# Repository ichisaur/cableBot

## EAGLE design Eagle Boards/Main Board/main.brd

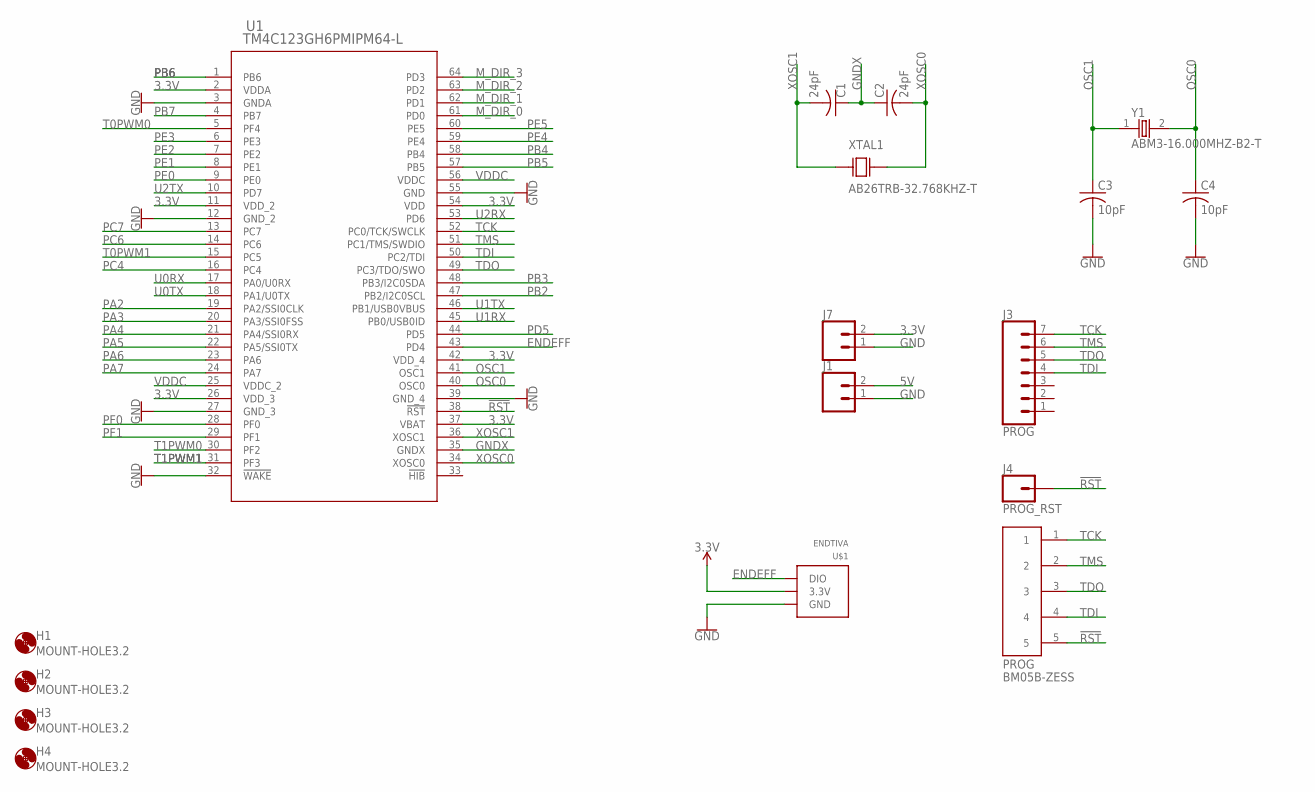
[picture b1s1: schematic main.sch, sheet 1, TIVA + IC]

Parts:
C1, C2: 24pF; C0805
C3, C4: 10pF; C0805
H1, H2, H3, H4: MOUNT-HOLE3.2; 3,2
J1, J7: CONN_02; 1X02
J3: PROG; 1X07
J4: PROG_RST; 1X01
PROG: BM05B-ZESS
U1: TM4C123GH6PMIPM64-L; PM64-L
U$1: ENDTIVA
XTAL1: AB26TRB-32.768KHZ-T; XTAL_AB26TRB-32.768KHZ-T
Y1: ABM3-16.000MHZ-B2-T; XTAL500X320X130N

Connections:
3.3V: J7.2, U1.2 (VDDA), U1.11 (VDD_2), U1.26 (VDD_3), U1.37 (VBAT), U1.42 (VDD_4), U1.54 (VDD), U$1.3.3V; also elsewhere on the board
5V: J1.2; also elsewhere on the board
!RST: J4.1, PROG.5, U1.38 (!RST); also elsewhere on the board
ENDEFF: U1.43 (PD4), U$1.DIO
GND: C3.2, C4.2, J1.1, J7.1, U1.3 (GNDA), U1.12 (GND_2), U1.27 (GND_3), U1.32 (!WAKE), U1.39 (GND_4), U1.55 (GND), U$1.GND; also elsewhere on the board
GNDX: C1.1, C2.1, U1.35 (GNDX)
M_DIR_0: U1.61 (PD0); also elsewhere on the board
M_DIR_1: U1.62 (PD1); also elsewhere on the board
M_DIR_2: U1.63 (PD2); also elsewhere on the board
M_DIR_3: U1.64 (PD3); also elsewhere on the board
OSC0: C4.1, U1.40 (OSC0), Y1.2
OSC1: C3.1, U1.41 (OSC1), Y1.1
PA2: U1.19 (PA2/SSI0CLK)
PA3: U1.20 (PA3/SSI0FSS)
PA4: U1.21 (PA4/SSI0RX)
PA5: U1.22 (PA5/SSI0TX)
PA6: U1.23 (PA6)
PA7: U1.24 (PA7)
PB2: U1.47 (PB2/I2C0SCL)
PB3: U1.48 (PB3/I2C0SDA)
PB4: U1.58 (PB4)
PB5: U1.57 (PB5)
PB6: U1.1 (PB6)
PB7: U1.4 (PB7)
PC4: U1.16 (PC4)
PC6: U1.14 (PC6)
PC7: U1.13 (PC7)
PD5: U1.44 (PD5)
PE0: U1.9 (PE0)
PE1: U1.8 (PE1)
PE2: U1.7 (PE2)
PE3: U1.6 (PE3)
PE4: U1.59 (PE4)
PE5: U1.60 (PE5)
PF0: U1.28 (PF0)
PF1: U1.29 (PF1)
T0PWM0: U1.5 (PF4); also elsewhere on the board
T0PWM1: U1.15 (PC5); also elsewhere on the board
T1PWM0: U1.30 (PF2); also elsewhere on the board
T1PWM1: U1.31 (PF3); also elsewhere on the board
TCK: J3.7, PROG.1, U1.52 (PC0/TCK/SWCLK)
TDI: J3.4, PROG.4, U1.50 (PC2/TDI)
TDO: J3.5, PROG.3, U1.49 (PC3/TDO/SWO)
TMS: J3.6, PROG.2, U1.51 (PC1/TMS/SWDIO)
U0RX: U1.17 (PA0/U0RX); also elsewhere on the board
U0TX: U1.18 (PA1/U0TX); also elsewhere on the board
U1RX: U1.45 (PB0/USB0ID); also elsewhere on the board
U1TX: U1.46 (PB1/USB0VBUS); also elsewhere on the board
U2RX: U1.53 (PD6)
U2TX: U1.10 (PD7)
VDDC: U1.25 (VDDC_2), U1.56 (VDDC); also elsewhere on the board
XOSC0: C2.2, U1.34 (XOSC0), XTAL1.2
XOSC1: C1.2, U1.36 (XOSC1), XTAL1.1

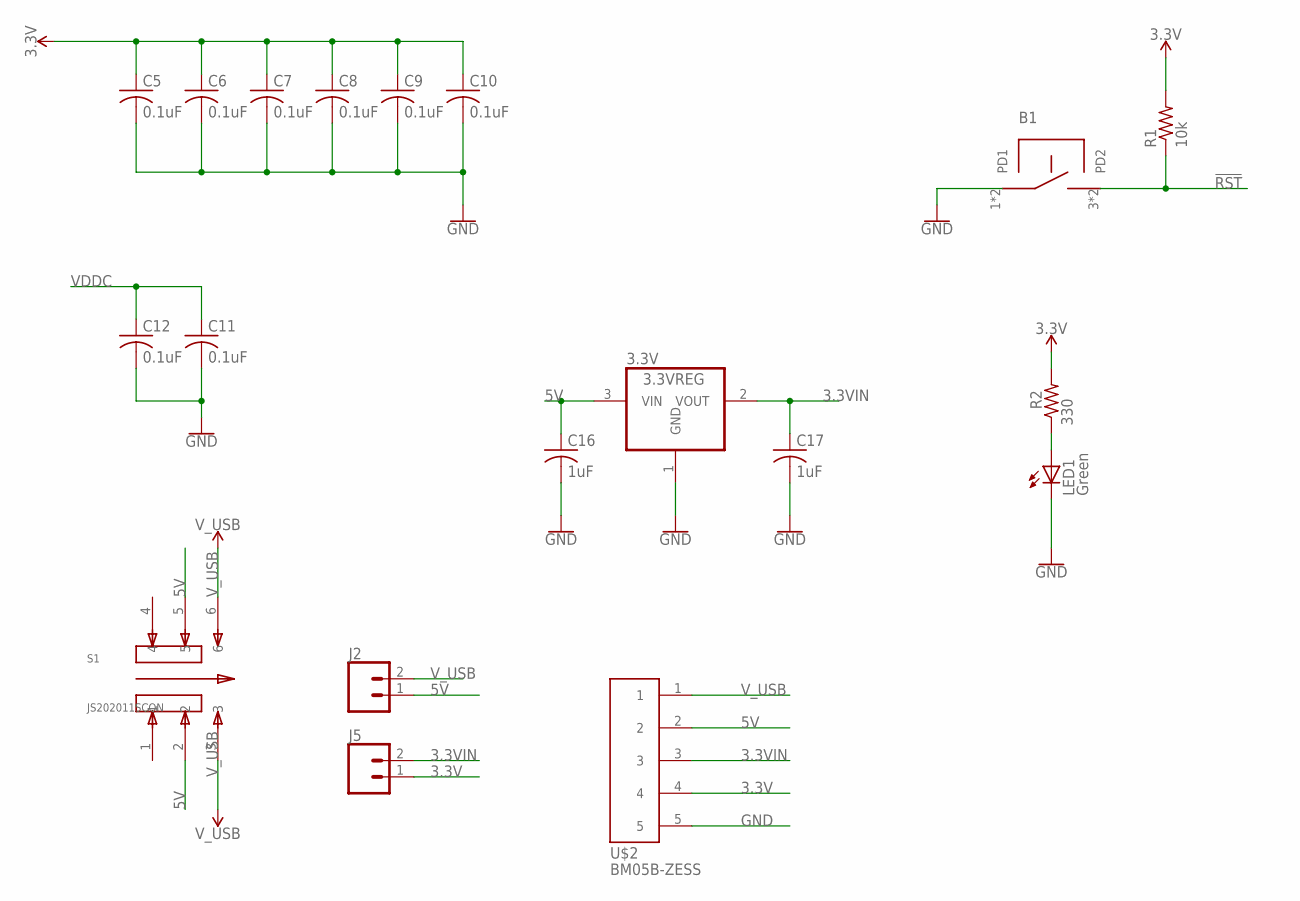
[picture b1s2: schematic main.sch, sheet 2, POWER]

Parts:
3.3V: 3.3VREG; SOT223
B1: B3S-1000; SWITCH
C5, C6, C7, C8, C9, C10, C11, C12: 0.1uF; C0805
C16, C17: 1uF; C0805
J2, J5: CONN_02; 1X02
LED1: Green; CHIP-LED0805
R1: 10k; R0603
R2: 330; R0805
S1: JS202011SCQN; SW_JS202011SCQN
U$2: BM05B-ZESS

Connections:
3.3V: C5.1, C6.1, C7.1, C8.1, C9.1, C10.1, J5.1, R1.2, R2.2, U$2.4; also elsewhere on the board
3.3VIN: 3.3V.2 (VOUT), C17.1, J5.2, U$2.3; also elsewhere on the board
5V: 3.3V.3 (VIN), C16.1, J2.1, S1.2, S1.5, U$2.2; also elsewhere on the board
!RST: B1.3 (PD2), B1.4 (PD2), R1.1; also elsewhere on the board
GND: 3.3V.1 (GND), B1.1 (PD1), B1.2 (PD1), C5.2, C6.2, C7.2, C8.2, C9.2, C10.2, C11.2, C12.2, C16.2, C17.2, LED1.C, U$2.5; also elsewhere on the board
unnamed: LED1.A, R2.1
VDDC: C11.1, C12.1; also elsewhere on the board
V_USB: J2.2, S1.3, S1.6, U$2.1; also elsewhere on the board

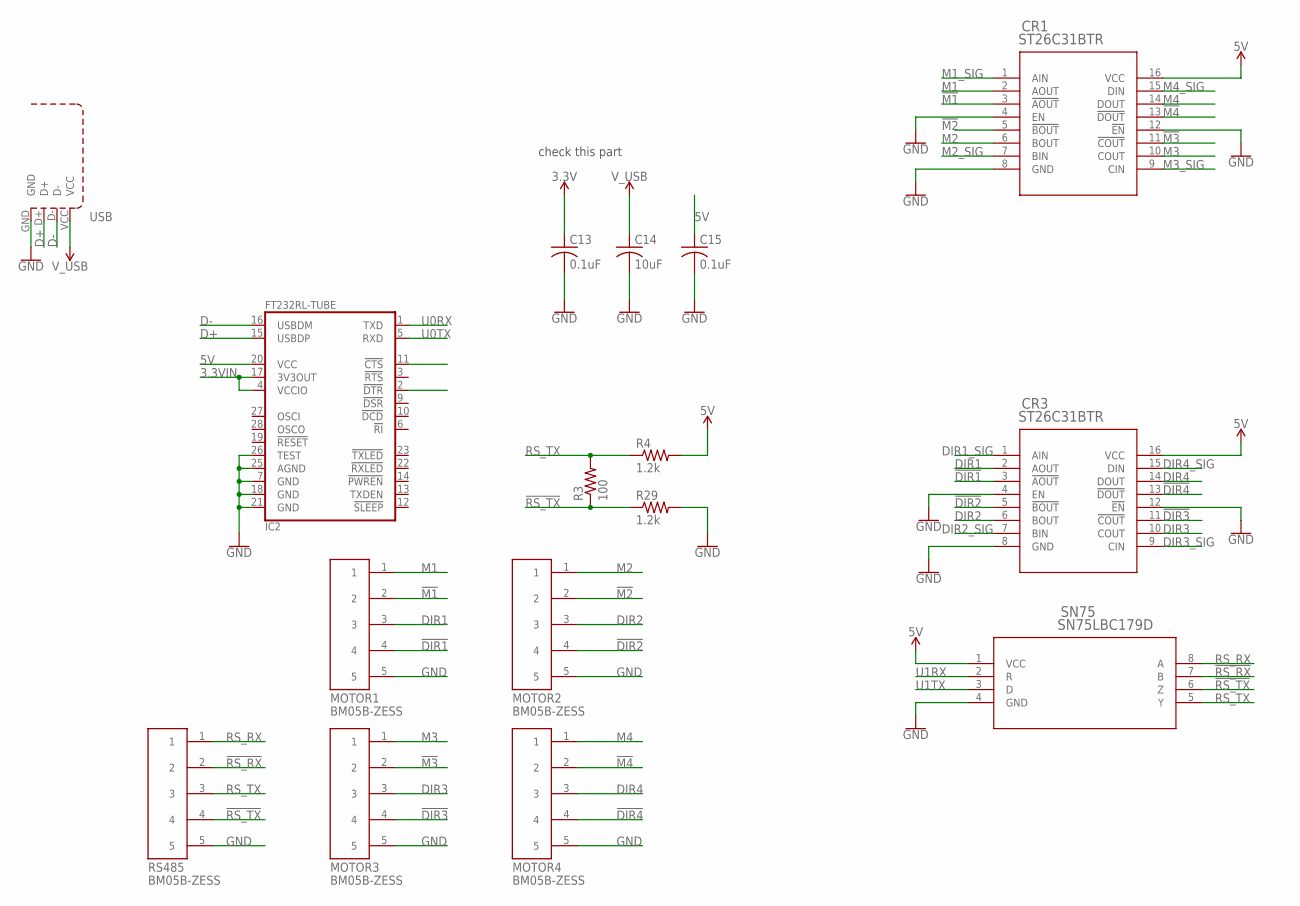
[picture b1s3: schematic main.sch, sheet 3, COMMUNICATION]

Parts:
C13, C15: 0.1uF; C0805
C14: 10uF; C0805
CR1, CR3: ST26C31BTR; TSSOP16
IC2: FT232RL-TUBE; SSOP28-LD
MOTOR1, MOTOR2, MOTOR3, MOTOR4: BM05B-ZESS
R3: 100; R0805
R4, R29: 1.2k; R0805
RS485: BM05B-ZESS
SN75: SN75LBC179D; D8
USB: ZX62MICROUSB; ZX62-AB-5PA(11)

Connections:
3.3V: C13.1; also elsewhere on the board
3.3VIN: IC2.4 (VCCIO), IC2.17 (3V3OUT); also elsewhere on the board
5V: C15.1, CR1.16 (VCC), CR3.16 (VCC), IC2.20 (VCC), R4.2, SN75.1 (VCC); also elsewhere on the board
!DIR1: CR3.3 (!AOUT), MOTOR1.4
!DIR2: CR3.5 (!BOUT), MOTOR2.4
!DIR3: CR3.11 (!COUT), MOTOR3.4
!DIR4: CR3.13 (!DOUT), MOTOR4.4
!M1: CR1.3 (!AOUT), MOTOR1.2
!M2: CR1.5 (!BOUT), MOTOR2.2
!M3: CR1.11 (!COUT), MOTOR3.2
!M4: CR1.13 (!DOUT), MOTOR4.2
!RS_RX: RS485.2, SN75.7 (B)
!RS_TX: R3.1, R29.1, RS485.4, SN75.6 (Z)
D+: IC2.15 (USBDP), USB.D+
D-: IC2.16 (USBDM), USB.D-
DIR1: CR3.2 (AOUT), MOTOR1.3
DIR1_SIG: CR3.1 (AIN); also elsewhere on the board
DIR2: CR3.6 (BOUT), MOTOR2.3
DIR2_SIG: CR3.7 (BIN); also elsewhere on the board
DIR3: CR3.10 (COUT), MOTOR3.3
DIR3_SIG: CR3.9 (CIN); also elsewhere on the board
DIR4: CR3.14 (DOUT), MOTOR4.3
DIR4_SIG: CR3.15 (DIN); also elsewhere on the board
GND: C13.2, C14.2, C15.2, CR1.4 (EN), CR1.8 (GND), CR1.12 (!EN), CR3.4 (EN), CR3.8 (GND), CR3.12 (!EN), IC2.7 (GND), IC2.18 (GND), IC2.21 (GND), IC2.25 (AGND), IC2.26 (TEST), MOTOR1.5, MOTOR2.5, MOTOR3.5, MOTOR4.5, R29.2, RS485.5, SN75.4 (GND), USB.GND; also elsewhere on the board
M1: CR1.2 (AOUT), MOTOR1.1
M1_SIG: CR1.1 (AIN); also elsewhere on the board
M2: CR1.6 (BOUT), MOTOR2.1
M2_SIG: CR1.7 (BIN); also elsewhere on the board
M3: CR1.10 (COUT), MOTOR3.1
M3_SIG: CR1.9 (CIN); also elsewhere on the board
M4: CR1.14 (DOUT), MOTOR4.1
M4_SIG: CR1.15 (DIN); also elsewhere on the board
RS_RX: RS485.1, SN75.8 (A)
RS_TX: R3.2, R4.1, RS485.3, SN75.5 (Y)
U0RX: IC2.1 (TXD); also elsewhere on the board
U0TX: IC2.5 (RXD); also elsewhere on the board
U1RX: SN75.2 (R); also elsewhere on the board
U1TX: SN75.3 (D); also elsewhere on the board
V_USB: C14.1, USB.VCC; also elsewhere on the board

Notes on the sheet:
check this part

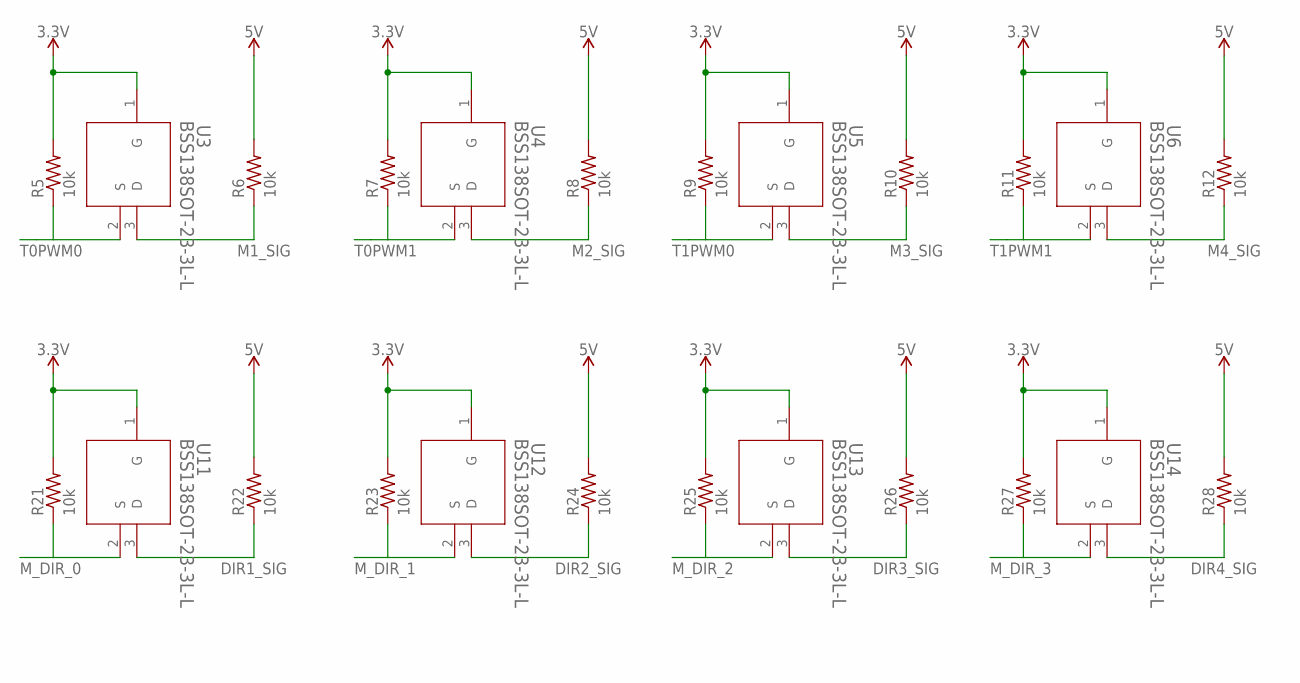
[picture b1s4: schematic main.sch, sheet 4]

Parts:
R5, R6, R7, R8, R9, R10, R11, R12, R21, R22, R23, R24, R25, R26, R27, R28: 10k; R0603
U3, U4, U5, U6, U11, U12, U13, U14: BSS138SOT-23-3L-L; SOT-23-3L-L

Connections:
3.3V: R5.2, R7.2, R9.2, R11.2, R21.2, R23.2, R25.2, R27.2, U3.1 (G), U4.1 (G), U5.1 (G), U6.1 (G), U11.1 (G), U12.1 (G), U13.1 (G), U14.1 (G); also elsewhere on the board
5V: R6.2, R8.2, R10.2, R12.2, R22.2, R24.2, R26.2, R28.2; also elsewhere on the board
DIR1_SIG: R22.1, U11.3 (D); also elsewhere on the board
DIR2_SIG: R24.1, U12.3 (D); also elsewhere on the board
DIR3_SIG: R26.1, U13.3 (D); also elsewhere on the board
DIR4_SIG: R28.1, U14.3 (D); also elsewhere on the board
M1_SIG: R6.1, U3.3 (D); also elsewhere on the board
M2_SIG: R8.1, U4.3 (D); also elsewhere on the board
M3_SIG: R10.1, U5.3 (D); also elsewhere on the board
M4_SIG: R12.1, U6.3 (D); also elsewhere on the board
M_DIR_0: R21.1, U11.2 (S); also elsewhere on the board
M_DIR_1: R23.1, U12.2 (S); also elsewhere on the board
M_DIR_2: R25.1, U13.2 (S); also elsewhere on the board
M_DIR_3: R27.1, U14.2 (S); also elsewhere on the board
T0PWM0: R5.1, U3.2 (S); also elsewhere on the board
T0PWM1: R7.1, U4.2 (S); also elsewhere on the board
T1PWM0: R9.1, U5.2 (S); also elsewhere on the board
T1PWM1: R11.1, U6.2 (S); also elsewhere on the board

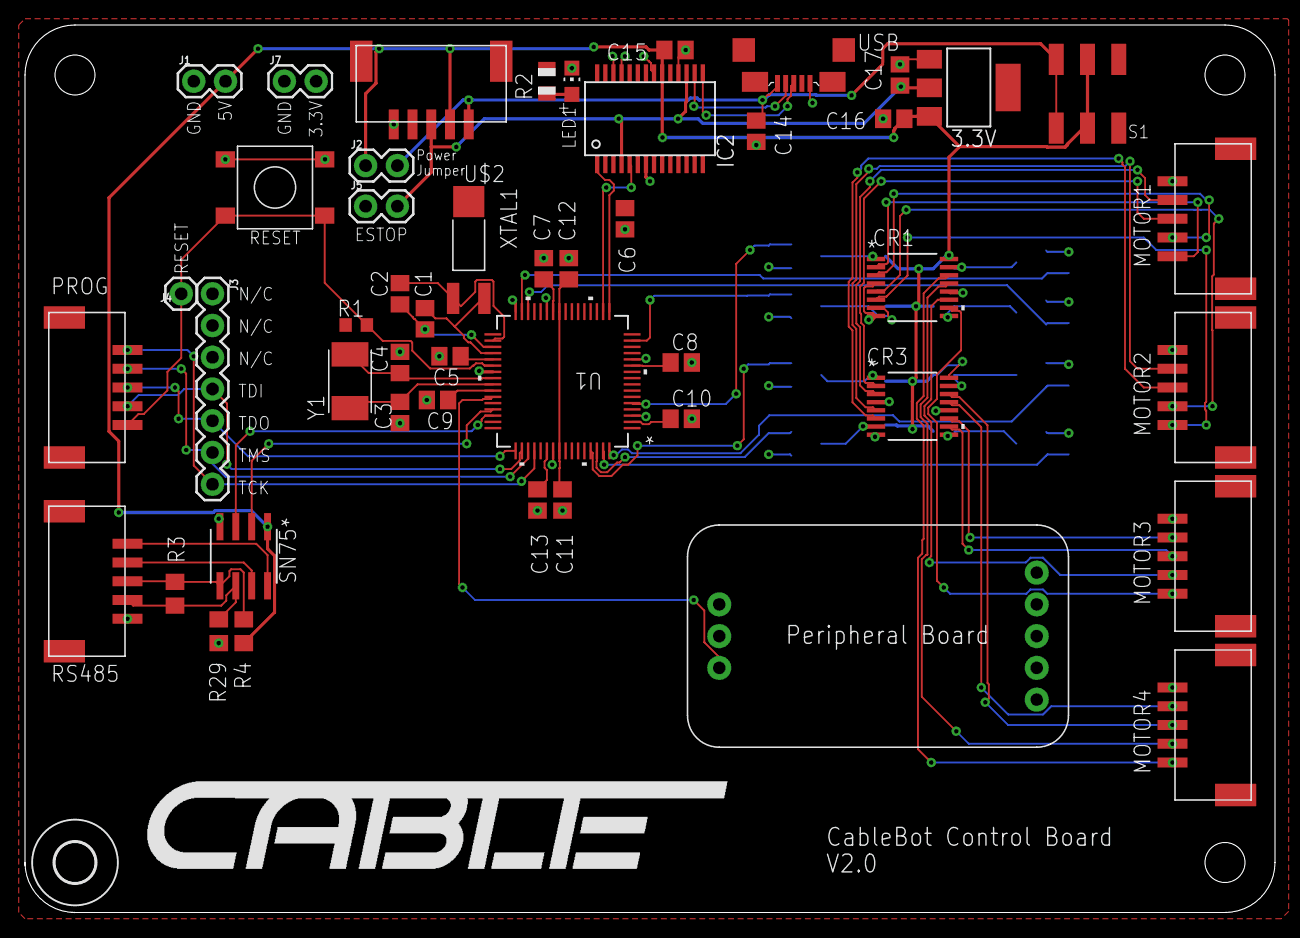
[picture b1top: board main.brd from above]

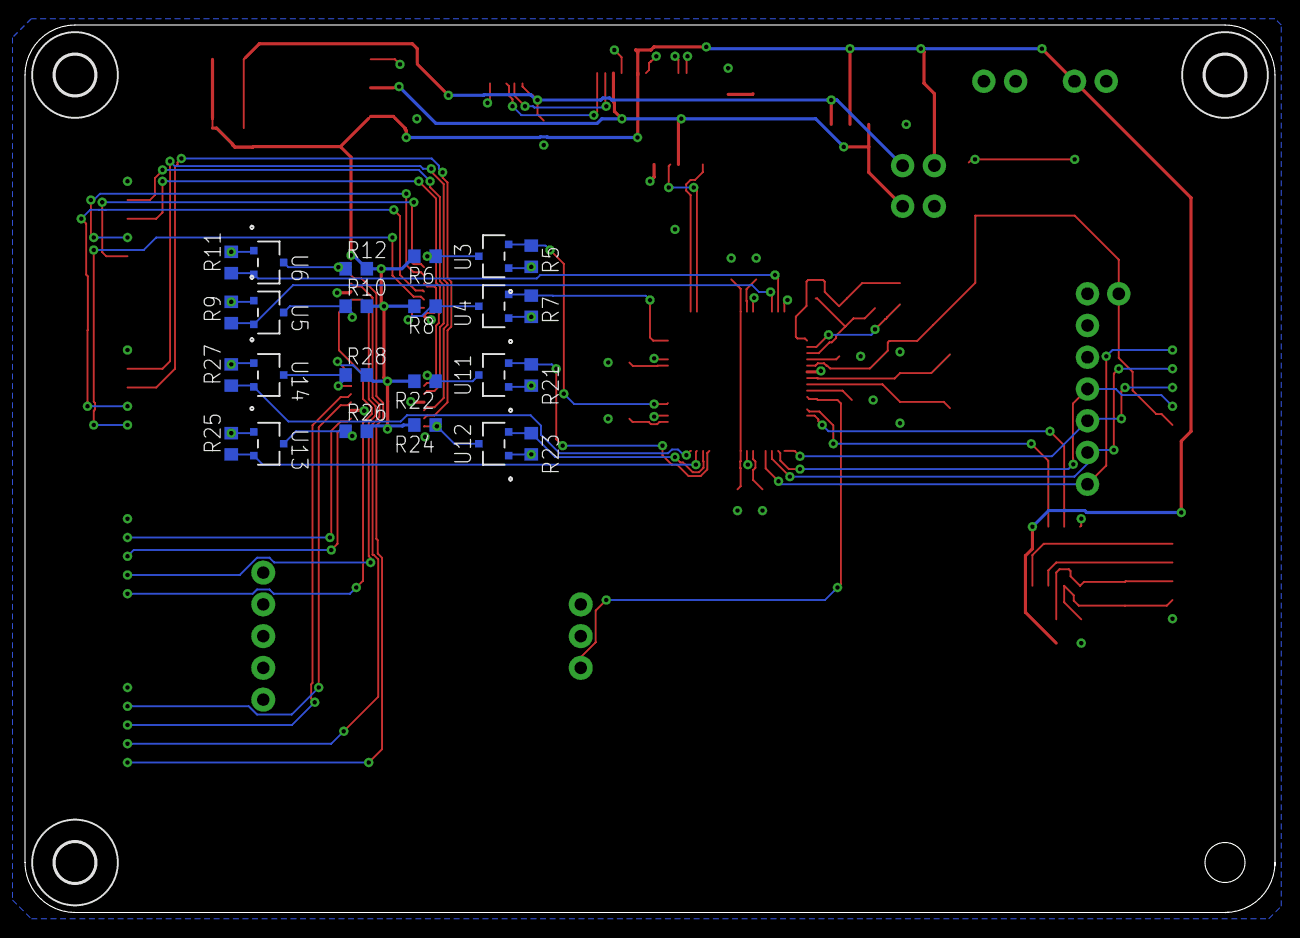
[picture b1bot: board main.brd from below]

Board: 2 copper layers, 100.0 x 71.0 mm, 76 parts (27 on the bottom side), 60 nets.

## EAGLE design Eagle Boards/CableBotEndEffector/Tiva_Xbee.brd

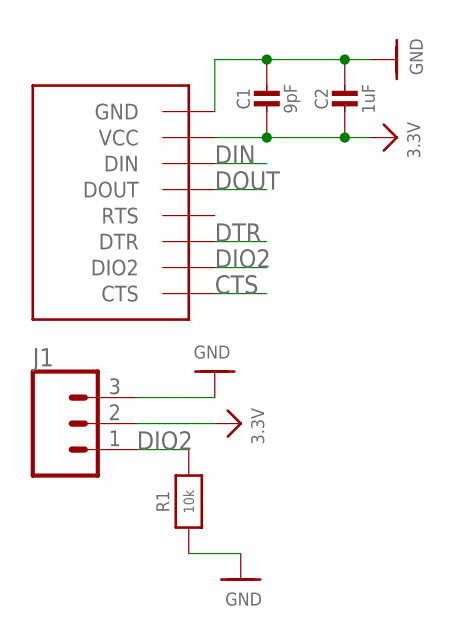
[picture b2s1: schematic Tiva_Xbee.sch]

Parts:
C1: 9pF; _0603
C2: 1uF; _0603
J1: CONN_03; 1X03
R1: 10k; _0603
U$1: XBEE3_DIO; XBEE3_MICRO

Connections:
3.3V: C1.2, C2.2, J1.2, U$1.VCC
CTS: U$1.CTS/DIO7 (CTS)
DIN: U$1.DIN/CONFIG/DIO14 (DIN)
DIO2: J1.1, R1.2, U$1.AD2/DIO2 (DIO2)
DOUT: U$1.DOUT/DIO13 (DOUT)
DTR: U$1.DTR/SLEEP_RQ/DIO8 (DTR)
GND: C1.1, C2.1, J1.3, R1.1, U$1.GND1 (GND), U$1.GND2 (GND), U$1.GND3 (GND), U$1.GND4 (GND), U$1.GND5 (GND), U$1.GND6 (GND)

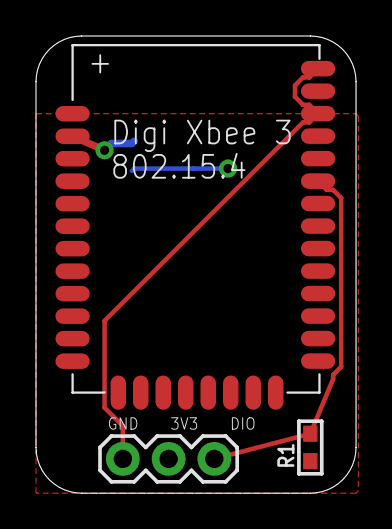
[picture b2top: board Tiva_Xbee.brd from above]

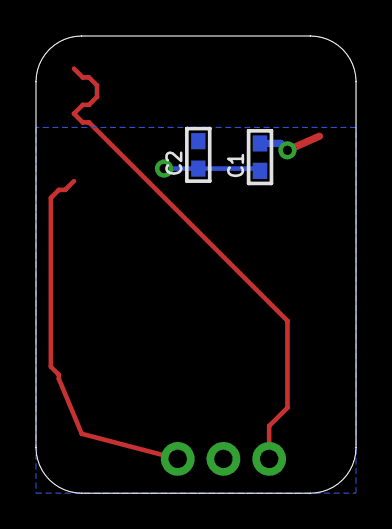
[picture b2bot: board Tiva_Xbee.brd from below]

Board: 2 copper layers, 17.8 x 25.4 mm, 5 parts (2 on the bottom side), 3 nets.

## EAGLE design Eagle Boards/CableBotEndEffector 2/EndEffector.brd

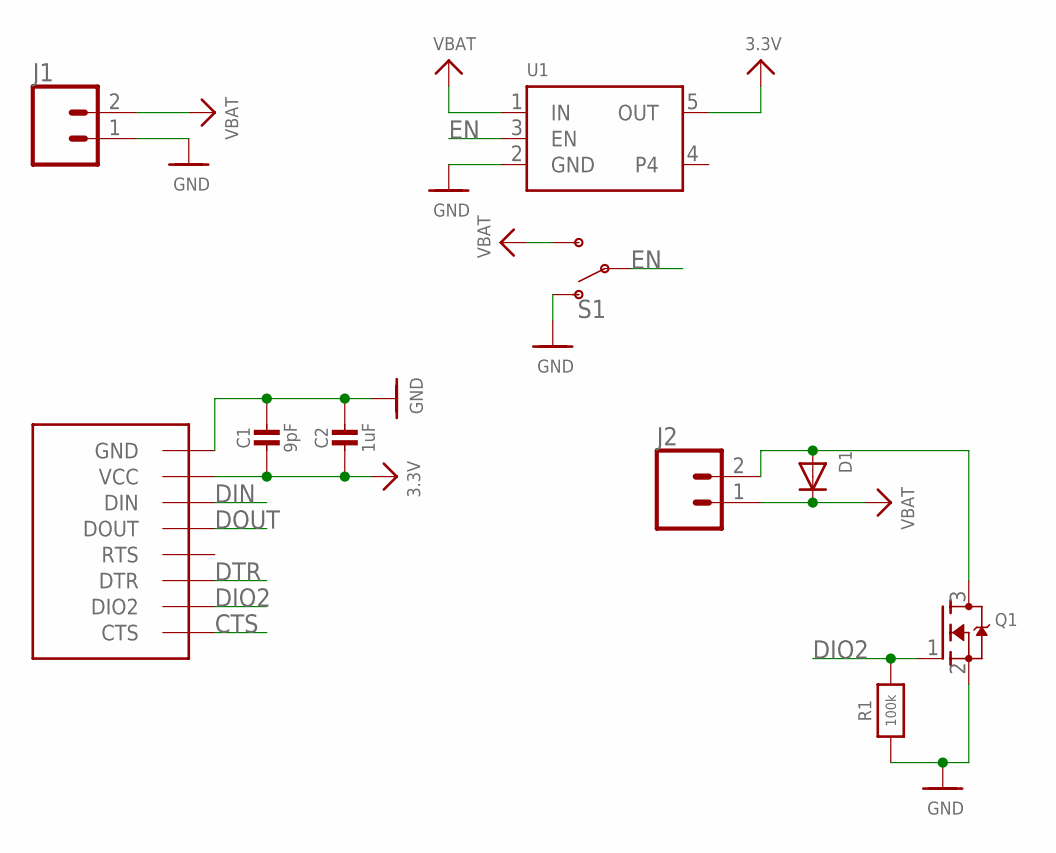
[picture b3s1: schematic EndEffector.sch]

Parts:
C1: 9pF; _0603
C2: 1uF; _0603
D1: DIODESOD-123; SOD-123
J1, J2: CONN_02; 1X02
Q1: MOSFET-NREFLOW; SOT23
R1: 100k; _0603
S1: SWITCH-SPDT-SMD-RIGHT-ANGLE; SWITCH_SPST_SMD_A
U1: VREG_SOT23-5; SOT23-5
U$1: XBEE3_DIO; XBEE3_MICRO

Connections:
3.3V: C1.2, C2.2, U1.5 (OUT), U$1.VCC
CTS: U$1.CTS/DIO7 (CTS)
DIN: U$1.DIN/CONFIG/DIO14 (DIN)
DIO2: Q1.1 (G), R1.2, U$1.AD2/DIO2 (DIO2)
DOUT: U$1.DOUT/DIO13 (DOUT)
DTR: U$1.DTR/SLEEP_RQ/DIO8 (DTR)
EN: S1.2, U1.3 (EN)
GND: C1.1, C2.1, J1.1, Q1.2 (S), R1.1, S1.1 (O), U1.2 (GND), U$1.GND1 (GND), U$1.GND2 (GND), U$1.GND3 (GND), U$1.GND4 (GND), U$1.GND5 (GND), U$1.GND6 (GND)
unnamed: D1.A, J2.2, Q1.3 (D)
VBAT: D1.C, J1.2, J2.1, S1.3 (S), U1.1 (IN)

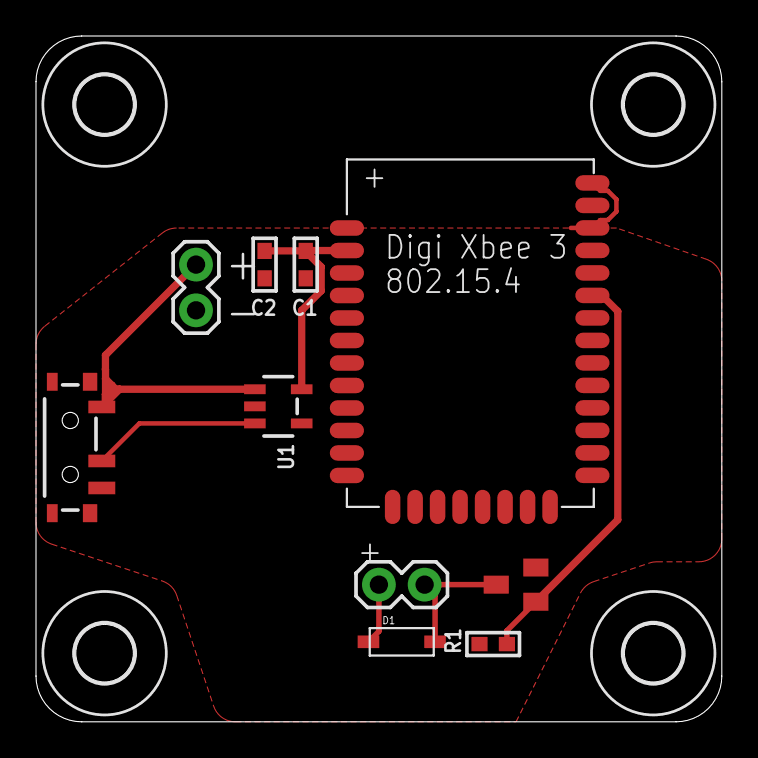
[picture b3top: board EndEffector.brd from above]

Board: 2 copper layers, 38.1 x 38.1 mm, 14 parts (0 on the bottom side), 6 nets.

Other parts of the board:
U$13, U$14, U$15, U$16: 3,2

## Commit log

2019-01-18 BYOM group1 folder
2019-01-20 added main.c
2019-01-21 UPDATED main.c
2019-01-21 pwm fix
2019-01-21 pwma and pwmc config cleanup
2019-01-21 inl pin config cleanup
2019-01-21 Revert "Update main.c"
    This reverts commit 892cddcca51696e9df26c6238c3d8480794f39d8.
2019-01-21 Revert "Revert "Update main.c""
    This reverts commit c5488760f1286f888c1dd49c9b77d63d5c78e6b5.
2019-01-21 Revert "Update main.c"
    This reverts commit b733a0eca9e7fd218a67054e3e62283663ca7c7e.
2019-01-21 Revert "Update main.c"
    This reverts commit 1bdc145443f287e94f3abad9a679c0f99fe5012f.
2019-01-21 PWM fixed
2019-01-21 interrupt testing
2019-01-21 working on interrupt
2019-01-21 Interrupt Troubleshooting
2019-01-22 Interrupts working
2019-01-22 ADC working (kinda)
2019-01-22 configure Timer3A
2019-01-22 timer interrupt
2019-01-23 Motor working
2019-01-23 some uart changes
2019-01-23 array write modifications
2019-01-24 Data Collection Working
2019-01-24 data
2019-01-24 Bit of processing
2019-01-24 Data from Other Team
2019-01-25 More correct data now
2019-01-25 Matlab Data Analysis
2019-03-10 gui and backend merged for single commands
2019-03-14 Add eagle .gitignore
2019-03-14 Fix .gitignore file
2019-03-14 Initial Commit Main Board
2019-04-10 finish most of board design prelim
2019-04-12 fix a few chips. add RS485 Hookup
2019-04-24 Update eagle files
2019-04-24 made documentation folder
2019-05-13 xbee boards
2019-05-16 commit pictures
2019-05-19 updated Xbee boards
2019-05-19 xbee board update
2019-05-21 clean up boards
2019-05-21 new boards
2019-05-21 final board prelim final design
2019-05-23 Fix Firmware
2019-05-23 Fix the not reading hwType bug. Now Echos hwType to buffer as well
2019-05-31 tivacode
2019-05-31 python code
2019-06-03 adding UART1
2019-06-06 changing the python code
2019-06-07 final code of TIVA
2019-06-07 comment on the main.c

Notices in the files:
parts and their libraries:
SparkFun-Connectors: Licensing: Creative Commons ShareAlike 4.0 International - https://creativecommons.org/licenses/by-sa/4.0
